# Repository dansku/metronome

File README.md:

# Metronome Electronics Kit (DIY)

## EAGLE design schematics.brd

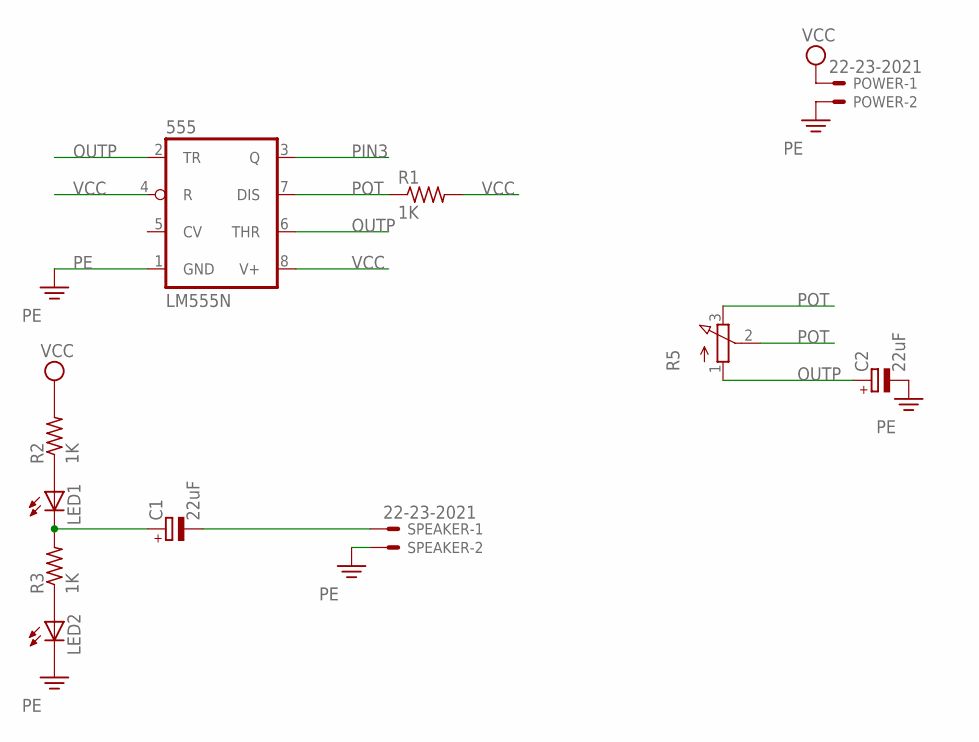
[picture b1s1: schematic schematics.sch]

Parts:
555: LM555N; DIL08
C1, C2: 22uF; E2,5-7
LED1, LED2: LED5MM
POWER: 22-23-2021
R1, R2, R3: 1K; 0207/10
R5: 3RP/1610N
SPEAKER: 22-23-2021

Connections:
unnamed: LED1.A, R2.1
unnamed: LED2.A, R3.1
unnamed: C1.-, SPEAKER.1
OUTP: 555.2 (TR), 555.6 (THR), C2.+, R5.1 (A)
PE: 555.1 (GND), C2.-, LED2.K (C), POWER.2, SPEAKER.2
PIN3: 555.3 (Q), C1.+, LED1.K (C), R3.2
POT: 555.7 (DIS), R1.1, R5.2 (S), R5.3 (E)
VCC: 555.4 (R), 555.8 (V+), POWER.1, R1.2, R2.2

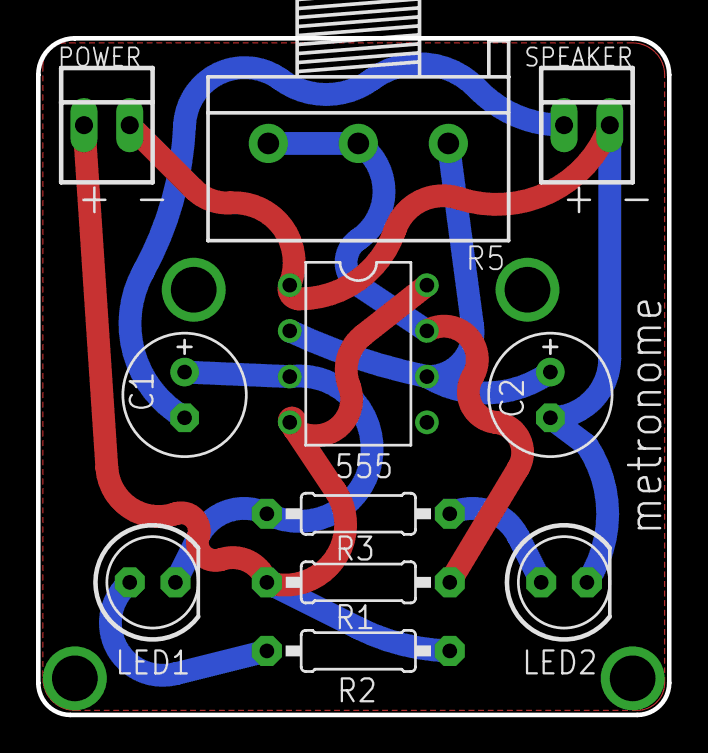
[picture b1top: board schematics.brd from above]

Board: 2 copper layers, 35.1 x 37.6 mm, 11 parts (0 on the bottom side), 8 nets.

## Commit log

2016-03-08 First commit. Still need to check component sizes.
2016-03-08 Add img.
2016-03-08 Update readme with img.
2016-03-13 Add round corners.
2016-03-13 Ground place.
2016-03-13 Update image
2016-06-02 Add wood picture.
2016-06-02 Add pic.
